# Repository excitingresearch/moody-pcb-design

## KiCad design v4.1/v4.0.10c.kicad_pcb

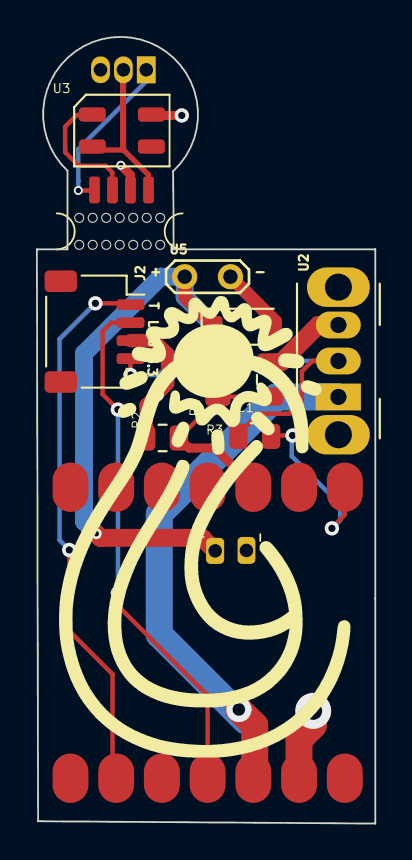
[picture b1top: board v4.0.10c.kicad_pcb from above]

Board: 2 copper layers, 18.8 x 43.7 mm, 14 parts (1 on the bottom side), 11 nets.

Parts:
C1: CC0402ZRY5V8BB104; C_0805_2012Metric
D1: SS14; D_SOD-123
D2: SK6812; LED_WS2812B-Mini_PLCC4_3.5x3.5mm
J1: SM04B-SRSS-TBLFSN; Breakout_conn
J2: SM04B-SRSS-TBLFSN; JST_SH_SM04B-SRSS-TB_1x04-1MP_P1.00mm_Horizontal
R1, R2: RC0402FR-0710KL; R_0805_2012Metric
R3: RC0402JR-07560RL; R_0805_2012Metric
U1: battery-xiao-esp32c3
U2: OS102011MA1QS1; SW_Slide_SPDT_Angled_CK_OS102011MA1Q
U3: TSIC206-TO92; TO-92L_Inline
U4: MOUDLE-SEEEDUINO-XIAO-ESP32C3; MOUDLE14P-SMD-2.54-21X17.8MM
U5: TestPoint_2Pads_Pitch2.54mm_Drill0.8mm
mouse-bite-2mm-slot: VAL**; mouse-bite-2mm-slot-langer

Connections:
/3.3V: D2.4 (DOUT), J1.4, U3.2 (Signal)
/B+: D1.1 (K), R1.1, U1.1 (+), U5.1 (+)
/D0: R3.1, U4.1 (PA02_A0_D0)
/D8: J2.1, U4.9 (PA7_A8_D8_SCK)
/D10: J2.2, U4.11 (PA6_A10_D10_MOSI)
/Licht: D2.3 (VDD), J1.2
/SW-OUT: J2.4, R3.2, U2.2
/Temp: J1.1, U3.1 (V+)
/esp-3.3: U2.1, U4.12 (3V3)
/esp-gnd: C1.2, D2.2 (DIN), J1.3, J2.3, R2.1, U1.2 (-), U2.3, U3.3 (GND), U4.13 (GND), U5.2 (-)
unnamed: C1.1, R1.2, R2.2, U4.3 (PA10_A2_D2)

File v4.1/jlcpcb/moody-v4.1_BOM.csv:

"Comment","Designator","Footprint","LCSC Part #","Manufacturer Part Number"
"100nF 50V X7R +/-10%","C1","0805","C49678","CC0805KRX7R9BB104"
"40V 1A Schottky diode","D1","SOD-123","C397616","DSL14"
"3.3V addressable RGB LED","D2","SMD3535-4P","C52941386","WS2812B-MINI-V6"
"JST SH 4-pin 1mm right-angle","J2","SMD P=1mm 1x4 right-angle","C160404","SM04B-SRSS-TB(LF)(SN)"
"10kOhm +/-1% 125mW","R1,R2","0805","C17414","0805W8F1002T5E"
"560Ohm +/-1% 125mW","R3","0805","C28636","0805W8F5600T5E"
"Seeed Studio XIAO ESP32C3","U4","LCC-14 castellated module","","113991054"

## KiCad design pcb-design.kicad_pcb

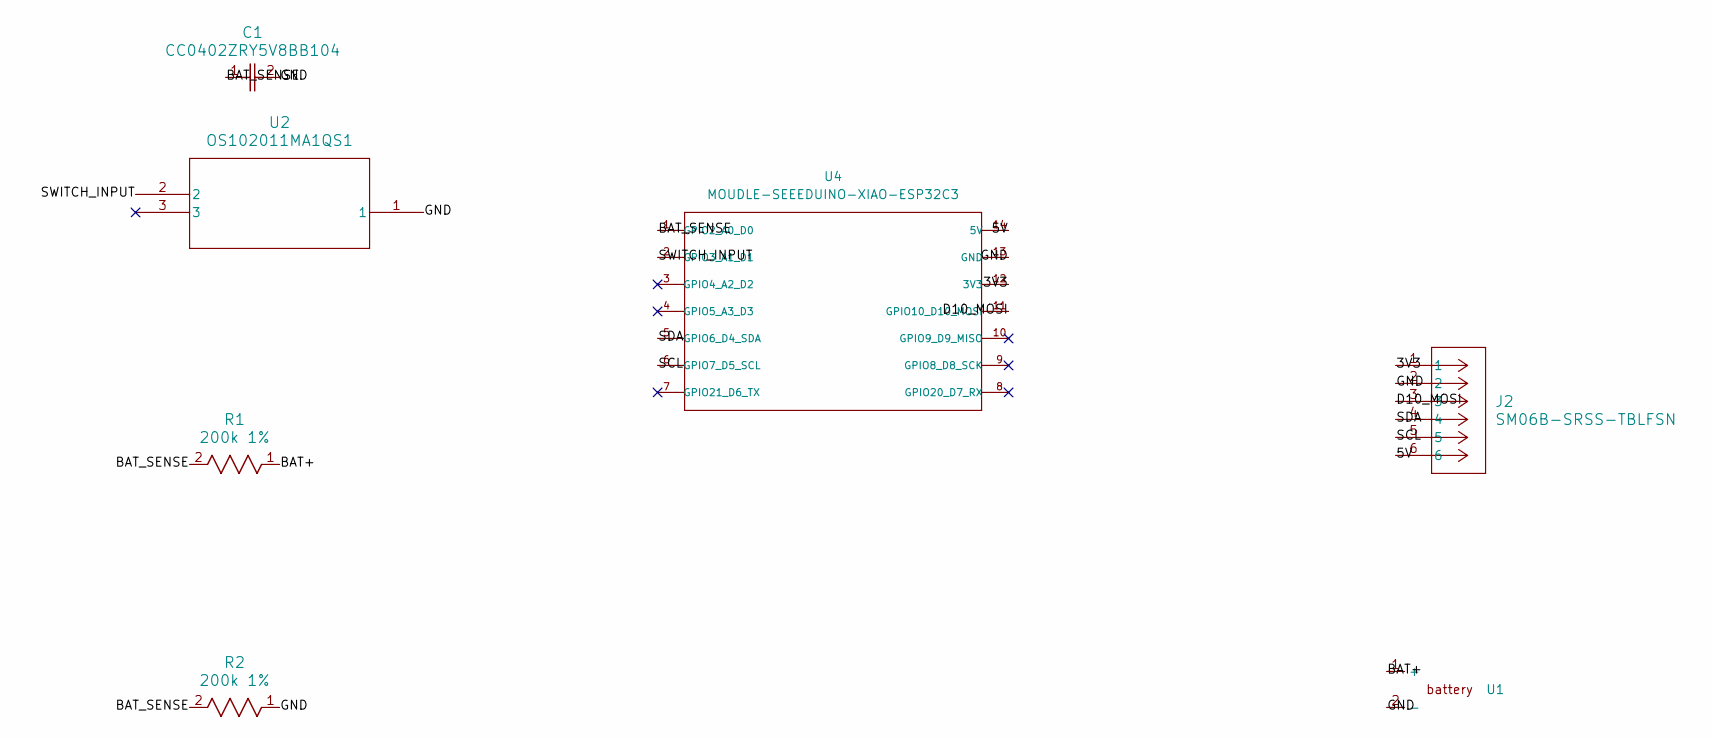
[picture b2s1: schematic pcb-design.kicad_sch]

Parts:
C1: CC0402ZRY5V8BB104; YAG_CC0402_YAG
J2: SM06B-SRSS-TBLFSN; CONN_SM06B-SRSS-TB_JST
R1, R2: 200k 1%; RC0402N_YAG
U1: battery-xiao-esp32c3
U2: OS102011MA1QS1; SWITCH_11MA1QS1
U4: MOUDLE-SEEEDUINO-XIAO-ESP32C3; MOUDLE14P-SMD-2.54-21X17.8MM

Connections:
3V3: J2.1, U4.12 (3V3)
5V: J2.6, U4.14 (5V)
BAT+: R1.1, U1.1 (+)
BAT_SENSE: C1.1, R1.2, R2.2, U4.1 (GPIO2_A0_D0)
D10_MOSI: J2.3, U4.11 (GPIO10_D10_MOSI)
GND: C1.2, J2.2, R2.1, U1.2 (-), U2.1, U4.13 (GND)
SCL: J2.5, U4.6 (GPIO7_D5_SCL)
SDA: J2.4, U4.5 (GPIO6_D4_SDA)
SWITCH_INPUT: U2.2, U4.2 (GPIO3_A1_D1)

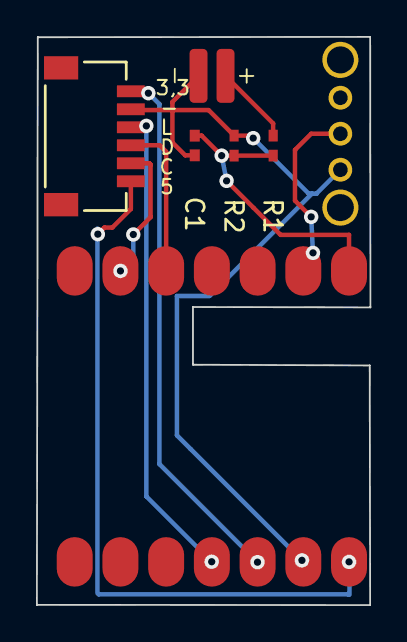
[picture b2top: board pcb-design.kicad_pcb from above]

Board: 2 copper layers, 18.5 x 31.6 mm, 7 parts (0 on the bottom side), 9 nets.

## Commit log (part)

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2024-01-18 v4.0.1
2024-01-18 jo WIP
2024-01-18 added via
2024-01-18 ready to almost make the pcb!!
2024-01-18 v4.0.1 in de maak lets hope no mistakes
2024-01-18 logfiles eruit
2024-03-07 v4.0.2
2024-03-07 update for jlcpcb
2024-03-07 ignore cache files
2024-04-08 3.3v new temp
2024-04-08 import SM04
2024-04-08 header for 4-new pcb...
2024-04-09 met transistor
2024-04-11 v.4.0.6
2024-04-11 co;;it v4.0.7
2024-04-18 v4.0.8
2024-04-19 mouse-bite-component
2024-04-19 saved
2024-04-22 mouse-bite + pcb-size
2024-04-25 v4.0.8 - weer een nieuwe versie aaa
2024-05-09 plus ground-header+tempsensor en light differently arranged
2024-05-09 tekstjes duidelijker
